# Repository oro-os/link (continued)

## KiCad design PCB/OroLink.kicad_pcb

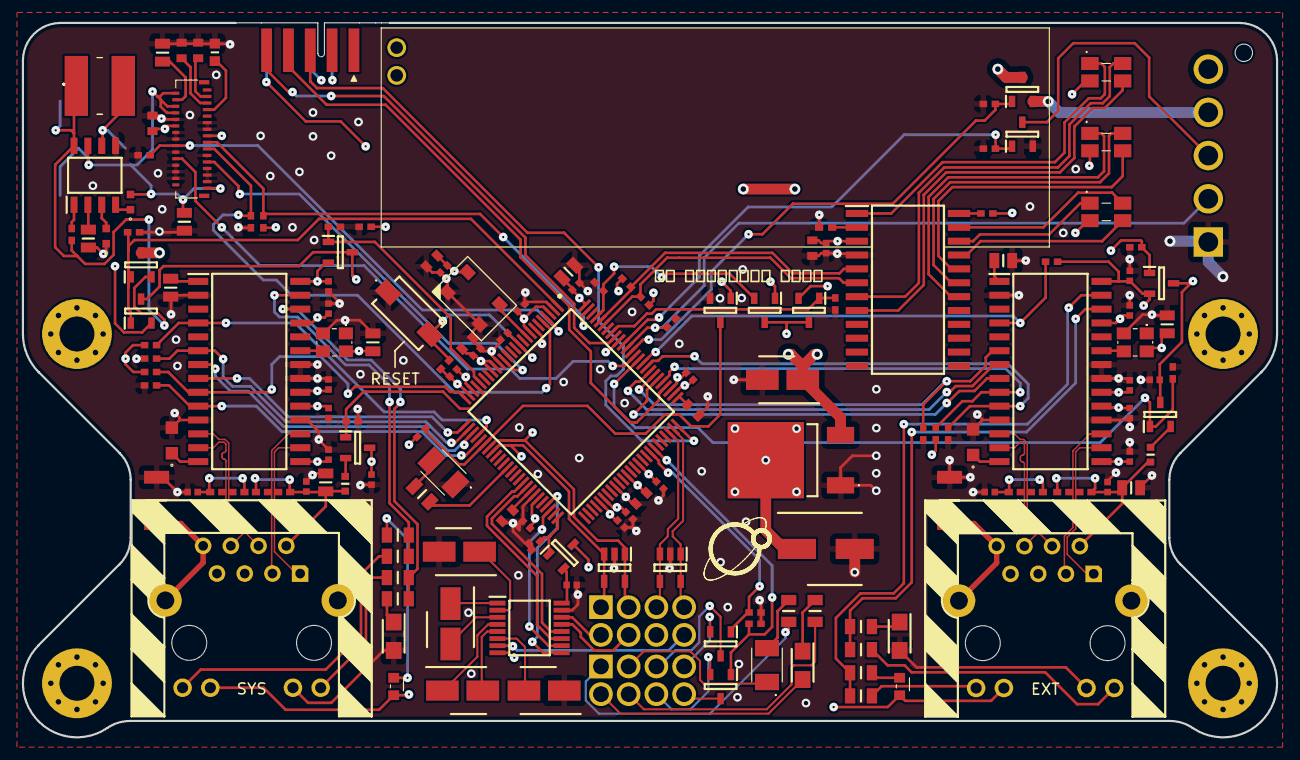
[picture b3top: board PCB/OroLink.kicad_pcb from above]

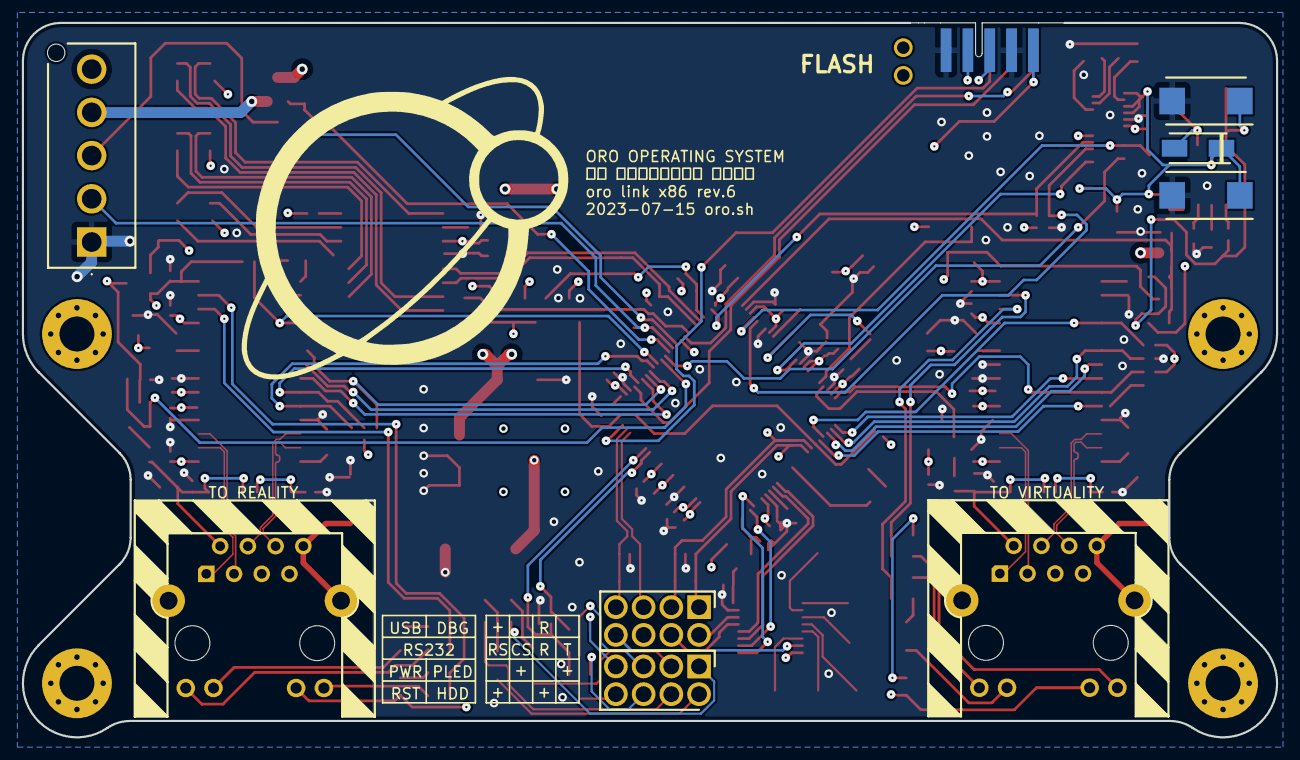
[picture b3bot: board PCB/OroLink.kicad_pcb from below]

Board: 4 copper layers, 114.9 x 65.4 mm, 167 parts (8 on the bottom side), 137 nets.

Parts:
C1, C3, C7, C8, C9, C10, C11, C12, C13, C14, C16, C32, C33, C34, C35, C36, C37, C38, C39, C44, C45, C46, C47, C48, C49, C50, C51, C57, C59: 0.1u; CAPC1005X33N
C2, C17, C20, C21, C23, C60: 1u; CAPC1608X90N
C4, C22, C24: 4.7u; CAPC2012X135N
C5, C6, C15: 2.2u; CAPC1608X90N
C18: 10u; CAPAE430X610N
C19: 22u; CAPAE660X800N
C25, C31, C43: 0.01u; CAPC2012X75N
C26: 0.047u; C1608_Commercial_Tight
C27: 0.001u; C1608_Commercial_Tight
C28, C29: 33u; CAPPM7343X310N
C30, C40, C42, C52: 10u; CAPC2012X135N
C41, C53: 1nF 3kV; CAPC4620X220N
C54, C55, C56, C58: 0.1u; CAPAE430X610N
D1, D2: ESDS302DBVR; SOT95P280X145-5N
D3: AZ1084CD-3.3TRG1; AZ1084CD33TRG1
D4: SS12; DIOM5227X250N
FB1: CD54NP-180MC; CD54NP180MC
FB2, FB3: BLM18BB600SZ1D; BLM18EG121SH1D
H1, H2, H3, H4: MountingHole_Pad; MountingHole_3.2mm_M3_Pad_Via
IC1: STM32F479VGT6; QFP50P1600X1600X160-100N
IC2, IC3, IC5, IC6, IC8, IC9, IC11, IC12, IC13, IC15, IC16: PMV20ENR; SOT95P230X110-3N
IC4: TPS6734ID; SOIC127P600X175-8N
IC7, IC10: ENC28J60-I_SO; SOIC127P1030X265-28N
IC14: SN75C3232EPWR; SOP65P640X120-16N
IC17: IS31FL3218-GRLS2; SOIC127P1036X265-24N
J1, J3: 67996-408HLF; HDRV8W89P254_2X4_1016X483X858P
J2: DF63-5P-3.96DSA; DF635P396DSA
J4: 3-2328724-1; 323287241_flipped
J5, J6: 74990101241
J7: 2P SHORT; 2P_SHORT
J8: STLINK-V3MINIE; 009159010061911
LED1, LED2: AA3528VRVFS/A; AA3528VRVFSA
LED3, LED4, LED6: CLM3C-WKW-CXAYA453; CLM3CWKWCXAYA453
LED5, LED7: APT1608VRCXF_A-5MAV; APT1608VRCXFA5MAV
LED8, LED9, LED10: 150120M173000
Q1, Q2, Q3: PMV20ENR; SOT95P230X110-3N
R1, R4, R5, R7, R8, R9, R11, R12, R21, R22, R23, R24, R25, R26, R27, R28, R29, R30, R32, R41, R42, R43, R44, R45, R47, R56, R57, R59, R60: 10k; RESC1005X40N
R2, R3: 4.7k; RESC1005X40N
R6, R10, R13, R37, R38, R52, R53: 1k; RESC2012X60N
R14: 510K; RESC1608X55N
R31, R46: 2.32k, <=1%; ERJP06__0805_
R33, R34, R35, R36, R48, R49, R50, R51: RMCF0201FT49R9; RESC1005X35N
R39, R40, R54, R55: 470R; RESC2012X60N
R58: 5.6K; RESC1105X40N
S1: TL6400AF160QJ
X1: 7P-26.000MBP-T
Y1, Y2: 25MHz; ASE24576MHZLCT

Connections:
+3V3: C1.2, C2.2, C4.1, C7.2, C8.2, C9.2, C10.2, C11.2, C12.2, C13.2, C14.2, C15.1, C16.2, C17.2, C19.1, C37.1, C49.1, D3.2 (OUTPUT), IC1.3 (VBAT), IC1.8 (VDD_1), IC1.17 (VREF+), IC1.18 (VDDA), IC1.24 (VDD_2), IC1.45 (VDD_3), IC1.55 (VDDDSI), IC1.56 (VCAPDSI), IC1.62 (VDD12DSI), IC1.65 (VDDUSB), IC1.77 (VDD_4), IC1.100 (VDD_5), IC3.3, IC6.3, IC8.3, IC9.3, IC11.3, IC12.3, IC15.3, IC16.3, J7.1, J8.10 (VCC), R1.1, R2.1, R3.1, R5.1, X1.6 (VCC)
+5V: C18.1, D3.3 (INPUT), IC2.3, IC5.3, J2.5
/COM Bus Header/C1+: C54.1, IC14.1 (C1+)
/COM Bus Header/C1-: C54.2, IC14.3 (C1-)
/COM Bus Header/C2+: C55.1, IC14.4 (C2+)
/COM Bus Header/C2-: C55.2, IC14.5 (C2-)
/COM Bus Header/CTS: IC1.47 (PB13), IC14.9 (ROUT2)
/COM Bus Header/EN: IC1.50 (PD8), IC15.1, R57.1
/COM Bus Header/EN_3V3: C57.1, IC14.16 (VCC), IC15.2
/COM Bus Header/RS232_CTS: IC14.8 (RIN2), J1.6
/COM Bus Header/RS232_RTS: IC14.7 (DOUT2), J1.8
/COM Bus Header/RS232_RX: IC14.13 (RIN1), J1.4
/COM Bus Header/RS232_TX: IC14.14 (DOUT1), J1.2
/COM Bus Header/RTS: IC1.48 (PB14), IC14.10 (DIN2)
/COM Bus Header/RX: IC1.42 (PB11), IC14.12 (ROUT1)
/COM Bus Header/TX: IC1.41 (PB10), IC14.11 (DIN1)
/COM Bus Header/V+: C56.1, IC14.2 (V+)
/COM Bus Header/V-: C58.2, IC14.6 (V-)
/External Ethernet/3V3_ETH: FB3.1, IC11.2
/External Ethernet/CS: IC1.80 (PA15), IC10.9 (~CS), R42.1
/External Ethernet/EN: IC1.91 (PD7), IC9.1, R45.1
/External Ethernet/ETH_TPIN+: IC10.13 (TPIN+), J6.6 (RD-), R51.1
/External Ethernet/ETH_TPIN-: IC10.12 (TPIN-), J6.4 (RD+), R50.1
/External Ethernet/ETH_TPOUT+: IC10.17 (TPOUT+), J6.3 (TD-), R49.1
/External Ethernet/ETH_TPOUT-: IC10.16 (TPOUT-), J6.1 (TD+), R48.1
/External Ethernet/GLED+: IC10.27 (LEDA), R52.2, R54.2
/External Ethernet/RJ_EARTH: C53.1, J6.8 (GNDPWR), J6.14 (MNT)
/External Ethernet/SCK: IC1.81 (PC10), IC10.8 (SCK)
/External Ethernet/SDI: IC1.83 (PC12), IC10.7 (SI)
/External Ethernet/SDO: IC1.82 (PC11), IC10.6 (SO), R43.2
/External Ethernet/VCC_EN: C43.1, C44.1, C45.1, C46.1, C47.1, C48.1, IC9.2, IC10.15 (VDDTX), IC10.19 (VDDRX), IC10.20 (VDDPLL), IC10.25 (VDDOSC), IC10.28 (VDD), J6.11 (GLED_A), LED7.2, R41.2, R42.2, Y2.4 (VDD)
/External Ethernet/XFRM_EN: IC1.86 (PD2), IC11.1, R47.2
/External Ethernet/YLED+: IC10.26 (LEDB), R53.2, R55.2
/External Ethernet/~INT: IC1.85 (PD1), IC10.4 (~INT), R41.1
/External Ethernet/~RST: IC1.84 (PD0), IC10.10 (~RESET), R44.2
/Front Panel Client/HDD+: J3.4, R13.1
/Front Panel Client/HDD-: J3.2, LED3.2
/Front Panel Client/PLED+: J3.1, R10.2
/Front Panel Client/PLED-: J3.3, LED2.1
/Front Panel Client/PWR+: J3.5, Q2.3
/Front Panel Client/PWR-: J3.7, Q2.2
/Front Panel Client/PWR_ON: IC1.68 (PC8), Q2.1, R11.1
/Front Panel Client/RESET: IC1.69 (PC9), Q3.1, R12.1
/Front Panel Client/RST+: J3.8, Q3.3
/Front Panel Client/RST-: J3.6, Q3.2
/Indicator Lights/EN: IC1.93 (PB4), IC16.1, R59.1
/Indicator Lights/EN_3V3: C59.1, C60.2, IC16.2, IC17.3 (VCC), LED8.2 (A_G), LED9.2 (A_G), LED10.2 (A_G), R60.1
/Indicator Lights/O1: IC17.7 (O1), LED8.4 (K_R)
/Indicator Lights/O2: IC17.8 (O2), LED8.3 (K_G)
/Indicator Lights/O12: IC17.18 (O12), LED9.1 (K_B)
/Indicator Lights/O13: IC17.19 (O13), LED9.4 (K_R)
/Indicator Lights/O14: IC17.20 (O14), LED9.3 (K_G)
/Indicator Lights/O15: IC17.21 (O15), LED10.3 (K_G)
/Indicator Lights/O16: IC17.22 (O16), LED10.1 (K_B)
/Indicator Lights/O17: IC17.23 (O17), LED10.4 (K_R)
/Indicator Lights/O18: IC17.1 (O18), LED8.1 (K_B)
/Indicator Lights/SCL: IC1.95 (PB6), IC17.6 (SCL), R2.2
/Indicator Lights/SDA: IC1.96 (PB7), IC17.5 (SDA), R3.2
/Microcontroller/BOOT0: IC1.97 (BOOT0), IC12.2, R4.2
/Microcontroller/BOOT1: IC1.31 (PB2), IC13.3, R5.2
/Microcontroller/DBGUART_RX: D1.1 (NC_1), D1.5 (I/O2), IC1.32 (PE7), J1.3, J8.7 (VCP_RX)
/Microcontroller/DBGUART_TX: D1.3 (NC_2), D1.4 (I/O1), IC1.33 (PE8), J1.1, J8.8 (VCP_TX)
/Microcontroller/SWCLK: IC1.79 (PA14), J8.4 (JCLK/SWCLK)
/Microcontroller/SWDIO: IC1.75 (PA13), J8.3 (JTMS/SWDIO)
/Microcontroller/SWO: IC1.92 (PB3), J8.5 (JTDO/SWO)
/Microcontroller/SYSETH_CS: IC1.25 (PA4), IC7.9 (~CS), R27.1
/Microcontroller/SYSETH_EN: IC1.21 (PA2), IC6.1, R30.1
/Microcontroller/SYSETH_MISO: IC1.27 (PA6), IC7.6 (SO), R28.2
/Microcontroller/SYSETH_SCK: IC1.26 (PA5), IC7.8 (SCK)
/Microcontroller/SYSETH_XFRM_EN: IC1.22 (PA3), IC8.1, R32.2
/Microcontroller/SYSTEH_MOSI: IC1.28 (PA7), IC7.7 (SI)
/Microcontroller/SYSTEH_~INT: IC1.29 (PB0), IC7.4 (~INT), R26.1
/Microcontroller/SYSTEH_~RST: IC1.30 (PB1), IC7.10 (~RESET), R29.2
/Microcontroller/USB_D+: D2.1 (NC_1), D2.5 (I/O2), IC1.74 (PA12), J1.7
/Microcontroller/USB_D-: D2.3 (NC_2), D2.4 (I/O1), IC1.73 (PA11), J1.5
/Microcontroller/VCAP1: C5.1, IC1.43 (VCAP1)
/Microcontroller/VCAP2: C6.1, IC1.76 (VCAP2)
/OLED Socket/+12V: C22.1, C27.2, C29.1, D4.1, IC4.7 (FB), J4.2, J4.6, J4.8, J4.31
/OLED Socket/CS: IC1.99 (PB9), J4.17, R23.2
/OLED Socket/DC: IC1.5 (PC14), J4.19, R22.1
/OLED Socket/ENABLE: IC1.1 (PE2), IC3.1, IC5.1, R25.1
/OLED Socket/SCK: IC1.87 (PD3), J4.22
/OLED Socket/SDI: IC1.15 (PC3), J4.23
/OLED Socket/VCC_EN: C23.2, IC3.2, J4.12, J4.15, R23.1
/OLED Socket/~RST: IC1.4 (PC13), J4.18, R21.1
/Power Supply/5VSB_ON: IC2.2, J2.4
/Power Supply/PSU_ON: J2.3, Q1.3
/Power Supply/PW_OK: IC1.89 (PD5), J2.2, R7.1
/Power Supply/PW_ON: IC1.90 (PD6), Q1.1, R9.1
/Power Supply/PW_SB: IC1.88 (PD4), IC2.1, R8.1
/System Ethernet/3V3_ETH: FB2.1, IC8.2
/System Ethernet/ETH_TPIN+: IC7.13 (TPIN+), J5.6 (RD-), R36.1
/System Ethernet/ETH_TPIN-: IC7.12 (TPIN-), J5.4 (RD+), R35.1
/System Ethernet/ETH_TPOUT+: IC7.17 (TPOUT+), J5.3 (TD-), R34.1
/System Ethernet/ETH_TPOUT-: IC7.16 (TPOUT-), J5.1 (TD+), R33.1
/System Ethernet/GLED+: IC7.27 (LEDA), R37.2, R39.2
/System Ethernet/RJ_EARTH: C41.1, J5.8 (GNDPWR), J5.14 (MNT)
/System Ethernet/VCC_EN: C31.1, C32.1, C33.1, C34.1, C35.1, C36.1, IC6.2, IC7.15 (VDDTX), IC7.19 (VDDRX), IC7.20 (VDDPLL), IC7.25 (VDDOSC), IC7.28 (VDD), J5.11 (GLED_A), LED5.2, R26.2, R27.2, Y1.4 (VDD)
/System Ethernet/YLED+: IC7.26 (LEDB), R38.2, R40.2
GND: C1.1, C2.1, C3.2, C4.2, C5.2, C6.2, C7.1, C8.1, C9.1, C10.1, C11.1, C12.1, C13.1, C14.1, C15.2, C16.1, C17.1, C18.2, C19.2, C20.1, C21.1, C22.2, C23.1, C24.1, C25.1, C26.1, C28.2, C29.2, C30.1, C31.2, C32.2, C33.2, C34.2, C35.2, C36.2, C37.2, C38.2, C39.2, C40.2, C41.2, C42.1, C43.2, C44.2, C45.2, C46.2, C47.2, C48.2, C49.2, C50.2, C51.2, C52.2, C53.2, C56.2, C57.2, C58.1, C59.2, C60.1, D1.2 (GND), D2.2 (GND), D3.1 (GND), IC1.2 (VSS_1), IC1.7 (VSS_2), IC1.16 (VSSA), IC1.23 (VSS_3), IC1.44 (VSS_4), IC1.59 (VSSDSI), IC1.78 (VSS_5), IC4.5 (GND), IC7.2 (VSS), IC7.11 (VSSRX), IC7.18 (VSSTX), IC7.21 (VSSPLL), IC7.22 (VSSOSC), IC10.2 (VSS), IC10.11 (VSSRX), IC10.18 (VSSTX), IC10.21 (VSSPLL), IC10.22 (VSSOSC), IC13.2, IC14.15 (GND), IC17.4 (GND), J2.1, J4.10, J4.11, J4.13, J4.14, J4.16, J4.20, J4.21, J4.24, J4.25, J4.26, J4.27, J4.28, J4.29, J5.10 (YLED_C), J6.10 (YLED_C), J8.6 (GND), J8.9 (NRST), LED1.1, LED4.2, LED6.2, Q1.2, R4.1, R7.2, R8.2, R9.2, R11.2, R12.2, R14.2, R21.2, R22.2, R25.2, R28.1, R29.1, R30.2, R31.2, R32.1, R43.1, R44.1, R45.2, R46.2, R47.1, R56.2, R57.2, R58.1, R59.2, S1.1 (COM), X1.1 (GND/AFC), X1.3 (GND), Y1.2 (GND/CASE), Y2.2 (GND/CASE)
unnamed: C20.2, J4.3
unnamed: C21.2, J4.5
unnamed: C24.2, J4.4
unnamed: C38.1, R35.2, R36.2
unnamed: C50.1, R50.2, R51.2
unnamed: C3.1, IC1.11 (NRST), R1.2, S1.2 (NO)
unnamed: IC1.37 (PE12), R6.1
unnamed: IC1.9 (PH0), X1.4 (CLK)
unnamed: C27.1, IC4.4 (COMP)
unnamed: IC4.1 (EN), R24.1
unnamed: D4.2, FB1.2, IC4.6 (OUT)
unnamed: C25.2, IC4.2 (REF)
unnamed: C26.2, IC4.3 (SS)
unnamed: C28.1, FB1.1, IC4.8 (VCC), IC5.2, R24.2
unnamed: IC7.23 (OSC1), Y1.3 (OUTPUT)
unnamed: IC7.14 (RBIAS), R31.1
unnamed: C30.2, IC7.1 (VCAP)
unnamed: IC10.23 (OSC1), Y2.3 (OUTPUT)
unnamed: IC10.14 (RBIAS), R46.1
unnamed: C42.2, IC10.1 (VCAP)
unnamed: IC12.1, IC13.1, J7.2, R56.1
unnamed: IC17.2 (R_EXT), R58.2
unnamed: IC17.24 (~SDB), R60.2
unnamed: J4.7, R14.1
unnamed: C39.1, C40.1, FB2.2, J5.2 (CTD), R33.2, R34.2
unnamed: J5.12 (GLED_C), R39.1
unnamed: J5.9 (YLED_A), R40.1
unnamed: C51.1, C52.1, FB3.2, J6.2 (CTD), R48.2, R49.2
unnamed: J6.12 (GLED_C), R54.1
unnamed: J6.9 (YLED_A), R55.1
unnamed: LED1.2, R6.2
unnamed: LED2.2, R10.1
unnamed: LED3.1, R13.2
unnamed: LED4.1, R38.1
unnamed: LED5.1, R37.1
unnamed: LED6.1, R53.1
unnamed: LED7.1, R52.1

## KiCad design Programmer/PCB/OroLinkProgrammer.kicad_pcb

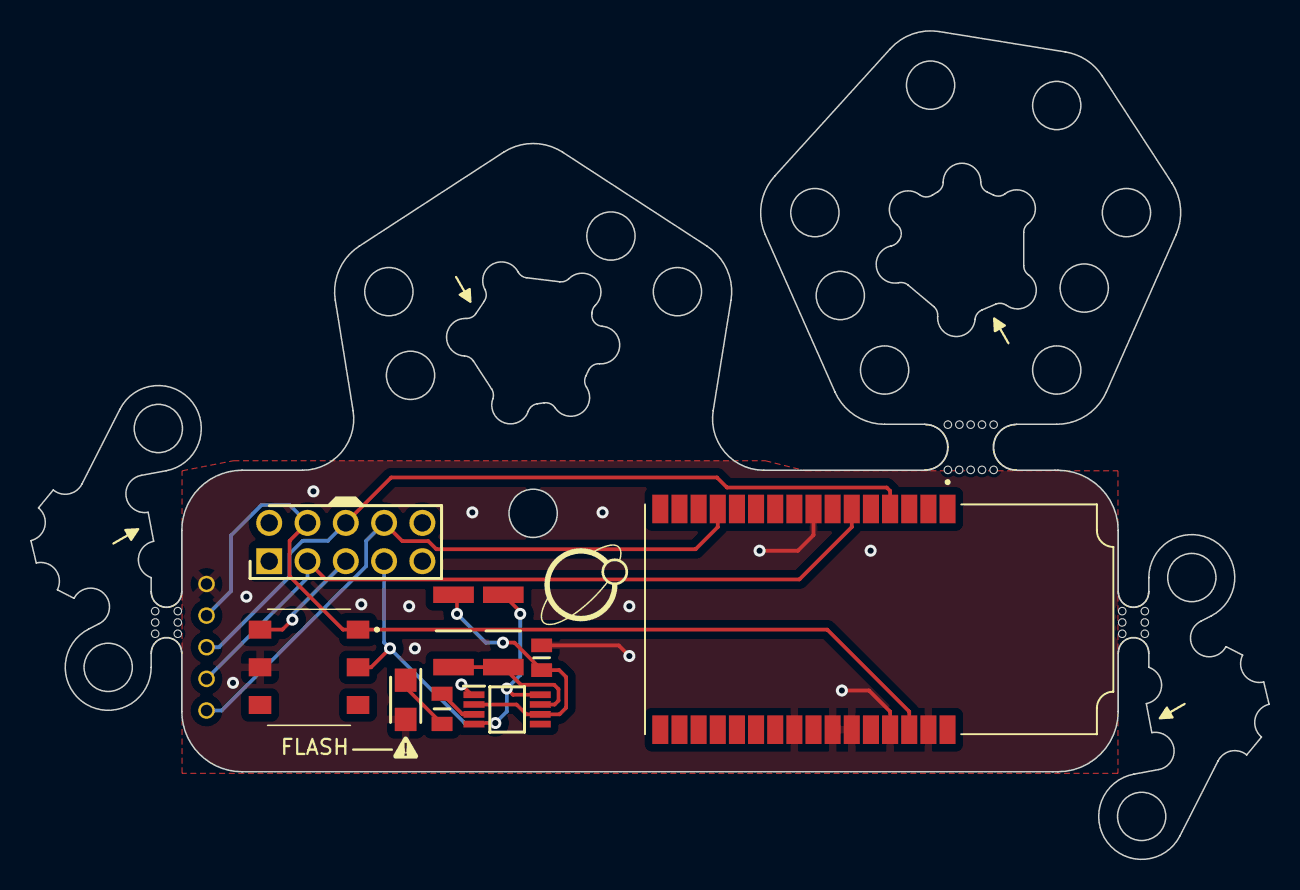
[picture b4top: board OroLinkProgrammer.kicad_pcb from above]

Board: 2 copper layers, 82.1 x 54.9 mm, 17 parts (0 on the bottom side), 11 nets.

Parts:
C1: 10u; CAPC2012X135N
DBG1, DBG2, DBG3, DBG4, DBG5: DebugPin
IC2: LMC555CMMX_NOPB; SOP65P490X110-8N
J1: 67996-110HLF; HDRV10W67P254_2X5_1270X483X858P
LED2: CLM3C-WKW-CXAYA453; CLM3CWKWCXAYA453
M1: STM32 STLINK V3MODS
R2, R3: 10k; RESC5025X65N
R4: 1k; RESC2012X60N
S2: 452403012014
mouse-bite-2mm-slot, mouse-bite-2mm-slot#2: VAL**; mouse-bite-2mm-slot
mouse-bite-3mm-slot: VAL**; mouse-bite-3mm-slot

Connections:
/BOOT0: J1.5, S2.4 (NO_2)
/BOOT1: IC2.4 (~RESET), IC2.8 (V+), J1.7, R2.1, S2.2 (COM_1)
/SWCLK: DBG3.1, J1.8, M1.13 (SWCLK)
/SWDIO: DBG2.1, J1.6, M1.4 (SWDIO)
/SWO: DBG4.1, J1.3, M1.6 (SWO)
/VREF: DBG1.1, J1.4, M1.30 (VCC), S2.1 (NO_1)
GND: C1.2, DBG5.1, IC2.1 (GND), LED2.2, M1.8 (GND), M1.24 (GND), M1.26 (GND), M1.27 (GND), M1.29 (GND), M1.31 (NRST), S2.5 (COM_2)
unnamed: IC2.7 (DISCHARGE), R2.2, R3.1
unnamed: IC2.3 (OUTPUT), R4.1
unnamed: C1.1, IC2.2 (~TRIGGER), IC2.6 (THRESHOLD), R3.2
unnamed: LED2.1, R4.2

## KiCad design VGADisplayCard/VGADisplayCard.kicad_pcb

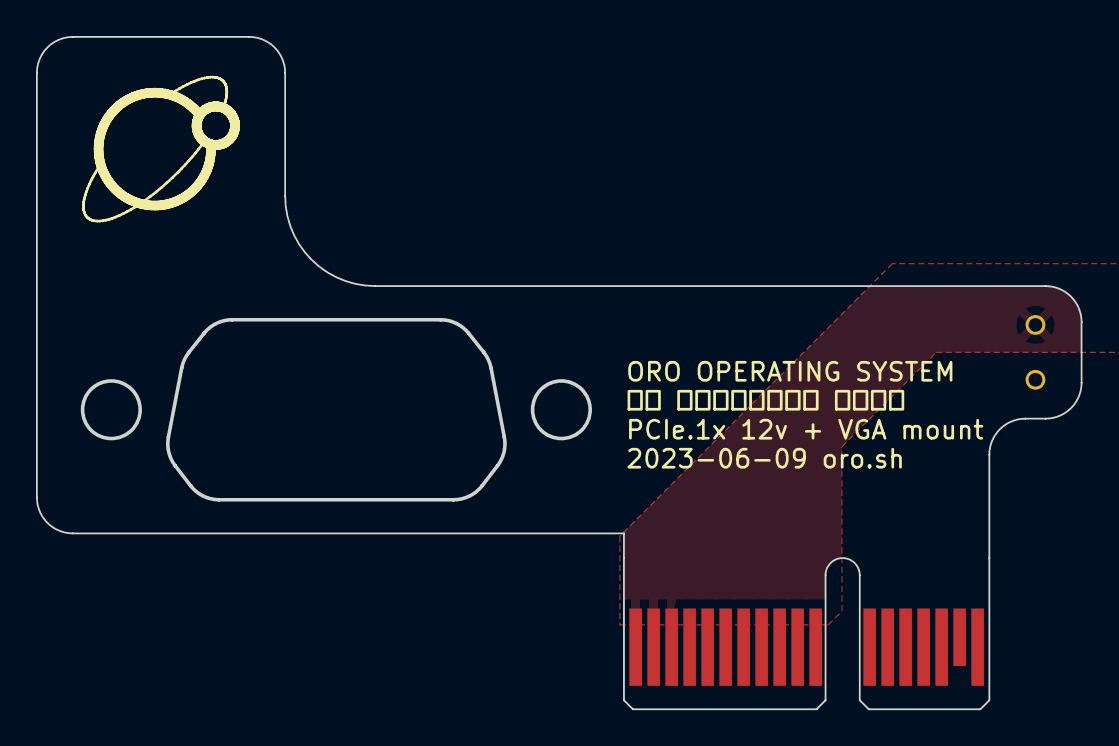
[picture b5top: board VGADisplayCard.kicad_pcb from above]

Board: 2 copper layers, 58.0 x 37.4 mm, 3 parts (0 on the bottom side), 2 nets, no tracks yet.

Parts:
J1, J3: DebugPin
J2: Bus_PCI_Express_x1; BUS_PCIexpress_x1

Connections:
/+12V: J1.1, J2.A2 (+12V), J2.A3 (+12V), J2.B1 (+12V), J2.B2 (+12V), J2.B3 (+12V)
/GND: J2.A4 (GND), J2.A12 (GND), J2.A15 (GND), J2.A18 (GND), J2.B4 (GND), J2.B7 (GND), J2.B13 (GND), J2.B16 (GND), J2.B18 (GND), J3.1
